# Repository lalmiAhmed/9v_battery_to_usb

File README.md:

# 9v battery to usb charger
this is a pcb deign fork for the coldpower USB charger

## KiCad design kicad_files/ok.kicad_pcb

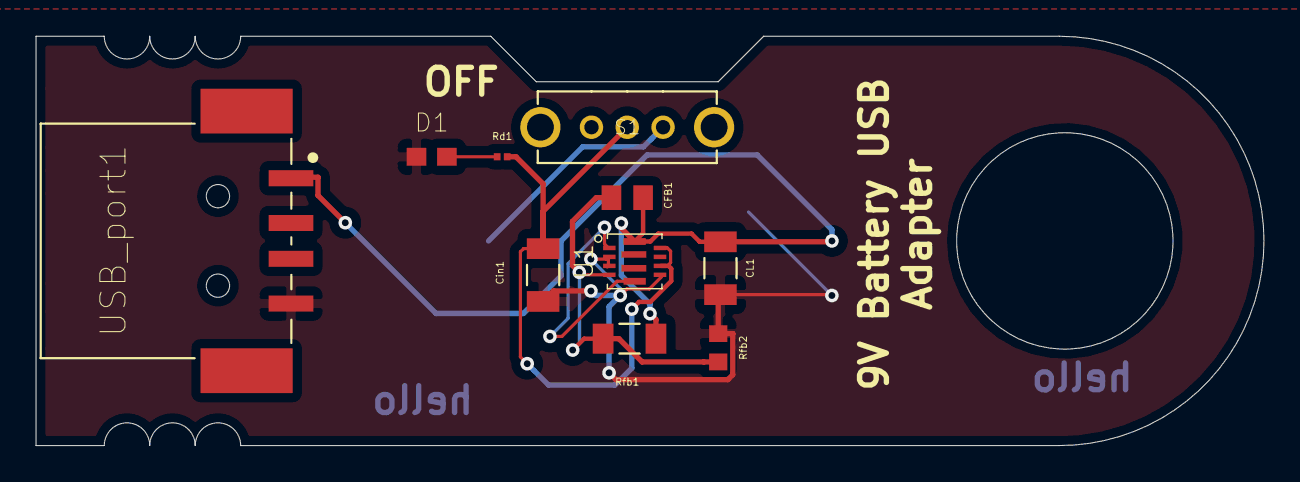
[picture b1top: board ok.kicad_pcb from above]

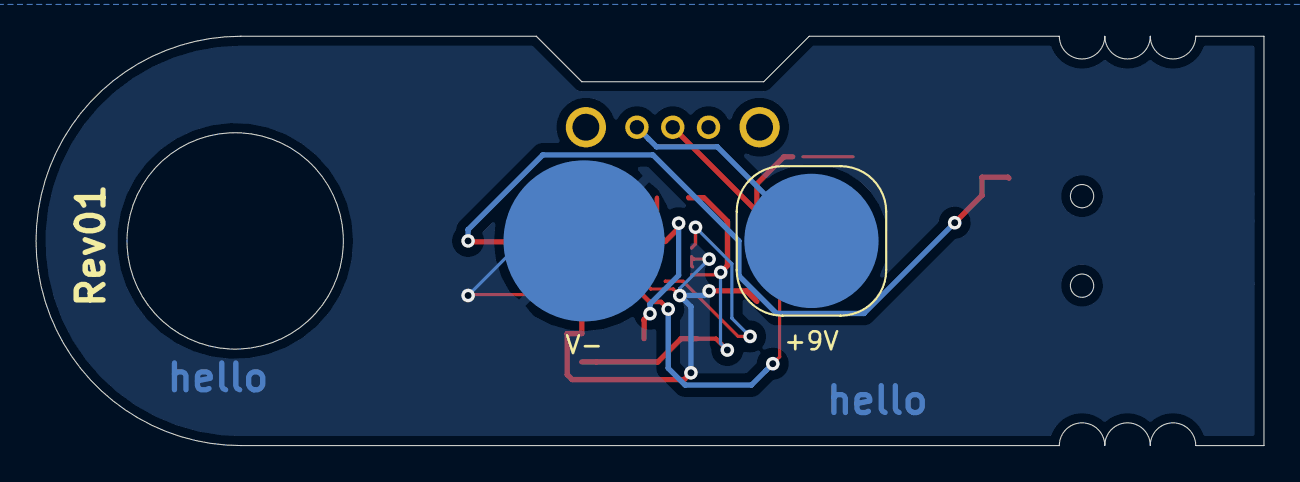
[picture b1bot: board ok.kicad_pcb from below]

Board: 2 copper layers, 68.6 x 22.9 mm, 12 parts (2 on the bottom side), 7 nets.

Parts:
+9V: Positive; BatteryContact_Keystone_269
CFB1: 18uF; CAPC2012X70N
CL1: 22uF; CAPC3216X229N
Cin1: 4.7uF; CAPC3216X178N
D1: HSMA-C120; 0603
Rd1: 1K; RESC0603X26N
Rfb1: 680K; RESC3216X70N
Rfb2: 120K; RESC1608X55N
S1: EG1213; SW_EG1213
U1: MYRGC; MYRGC_v01
USB_port1: UJ2-AH-1-SMT; CUI_UJ2-AH-1-SMT
V-: Negative; BatteryContact_Keystone_261

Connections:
+9V: +9V.1, S1.1
GND: CL1.2, Cin1.1, D1.1, Rfb2.2, U1.2, U1.3, U1.5, USB_port1.4, V-.1
unnamed: CFB1.1, Rfb1.2, Rfb2.1, U1.4
unnamed: CFB1.2, CL1.1, Rfb1.1, U1.10, USB_port1.1
unnamed: Cin1.2, Rd1.1, S1.2, U1.6, U1.8
unnamed: D1.2, Rd1.2
unnamed: U1.1, U1.9

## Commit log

2022-08-07 adding kicad files
2022-09-03 organizing files
2022-09-03 updating kicad files
2022-09-03 adding descriptions
2022-09-03 nothing
